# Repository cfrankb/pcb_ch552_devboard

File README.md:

# CH552 DEVBOARD

## Introduction

This is a pcb design for a CH552 DEVBOARD. The board is intended to aid in the development of firmware/prototype for the CH552 and CH554 microcontrollers.

* The Power Switch (Workflow Optimization):
The CH552 enters ISP (programming) mode based on power-on state with a specific pin held. Constantly pulling a USB cable wears out the connector and is inefficient. Your switch demonstrates mechanical sympathy and an understanding of the iterative development cycle.

* The "Ground Forest" (Signal Integrity):
Adding 12x GND pins isn't overkill—it's professional. It allows you to clip a logic analyzer, an oscilloscope probe, and multiple peripherals simultaneously without creating a "rat's nest" of wires sharing a single pin.

* The "Ground Forest" (Signal Integrity): 
 Having 4 LEDs dedicated to the MCU pins allows for immediate visual confirmation of state machines or "heartbeat" signals without needing to wire up external breadboard components.

https://github.com/cfrankb/ch552_drivers/

## Schematic

## Features

 * 4 led to provide indicators
 * 12x GND pins
 * 6x 3.3v pins
 * 6x 5v pins
 * ON/OFF button
 * BOOT and RESET buttons

## Part List

|     | Part #        | REF#                   | Package            |
| --- | ------------- | ---------------------- | ------------------ |
| 1x  | 10u C         | C3                     | 0805               |
| 2x  | 100n C        | C1, C2                 | 1206               |
| 2x  | 10k Resistor  | R1, R4                 | 0805               |
| 6x  | 1k Resistor   | R2, R3, R5, R6, R7, R8 | 0805               |
| 1x  | Green Led     | D1                     | 0805               |
| 5x  | Leds          | D2, D3, D4, D5, D6     | 0805               |
| 1x  | CH552G/CH554G | U1                     | SOP16              |
| 2x  | button        | SW1, SW2               | 6x6x4.3mm DIP      |
| 1x  | USB Connector | J1                     | USB 2.0 Female DIP |
| 1x  | 1x07          | J2                     | 2.54mm pins DIP    |
| 1x  | 2x03          | J3, J5, J6, J7         | 2.54mm pins DIP    |
| 1x  | 1x05          | J4                     | 2.54mm pins DIP    |
| 1x  | 1x04          | J8                     | 2.54mm pins DIP    |
| 1x  | 1x03          | J9                     | SS12D00 DIP *      |

\* You can also use a 2.54mm pin header with a jumper cap.

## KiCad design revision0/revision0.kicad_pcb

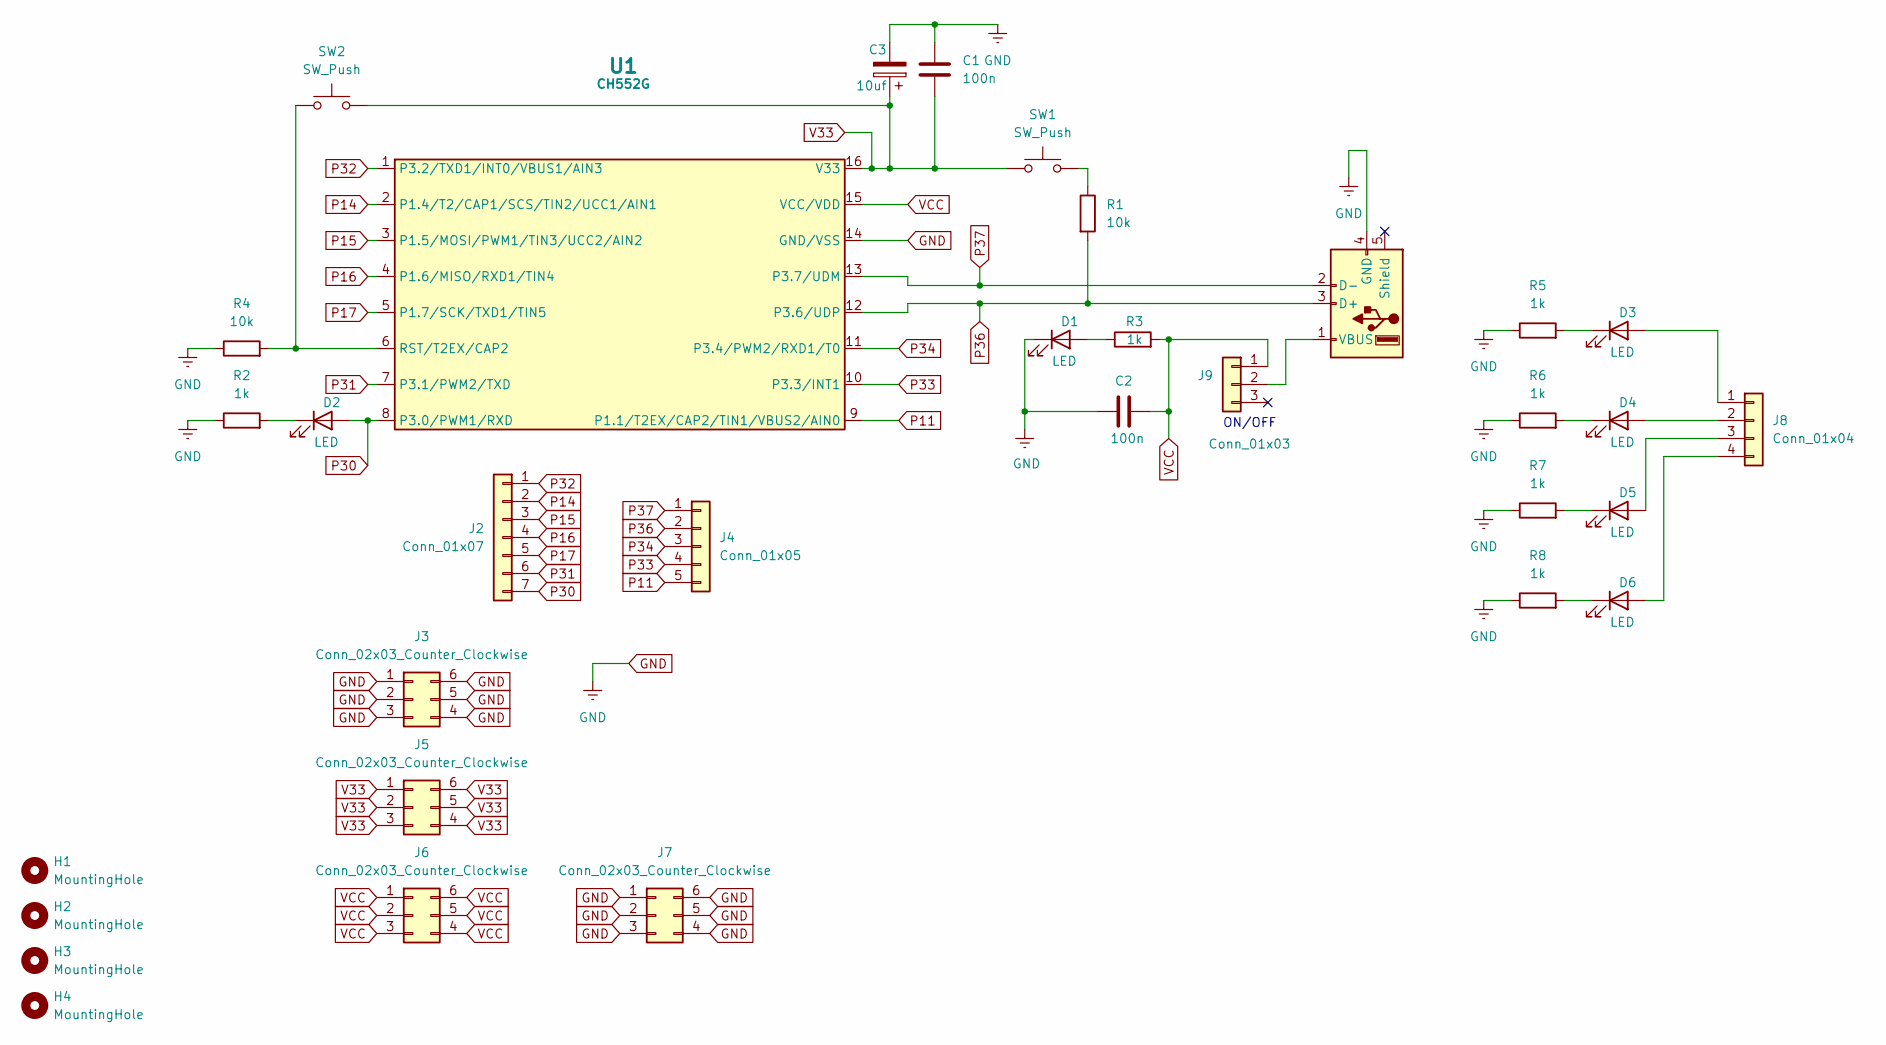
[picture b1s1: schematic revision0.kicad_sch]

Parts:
C1, C2: 100n; C_1206_3216Metric_Pad1.33x1.80mm_HandSolder
C3: 10uf; C_0805_2012Metric_Pad1.18x1.45mm_HandSolder
D1, D2, D3, D4, D5, D6: LED; LED_0805_2012Metric_Pad1.15x1.40mm_HandSolder
H1, H2, H3, H4: MountingHole; MountingHole_3mm
J1: USB1; USB_A_Molex_67643_Horizontal
J2: Conn_01x07; PinHeader_1x07_P2.54mm_Vertical
J3, J5, J6, J7: Conn_02x03_Counter_Clockwise; PinHeader_2x03_P2.54mm_Vertical
J4: Conn_01x05; PinHeader_1x05_P2.54mm_Vertical
J8: Conn_01x04; PinHeader_1x04_P2.54mm_Vertical
J9: Conn_01x03; PinHeader_1x03_P2.54mm_Vertical
R1, R4: 10k; R_0805_2012Metric_Pad1.20x1.40mm_HandSolder
R2, R3, R5, R6, R7, R8: 1k; R_0805_2012Metric_Pad1.20x1.40mm_HandSolder
SW1, SW2: SW_Push; SW_PUSH_6mm_H4.3mm
U1: CH552G; SOP-16_4.55x10.3mm_P1.27mm

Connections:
GND: C1.1, C2.1, C3.2, D1.1 (K), J1.4 (GND), J3.1, J3.2, J3.3, J3.4, J3.5, J3.6, J7.1, J7.2, J7.3, J7.4, J7.5, J7.6, R2.1, R4.1, R5.1, R6.1, R7.1, R8.1, U1.14 (GND/VSS)
unnamed: D1.2 (A), R3.1
unnamed: D2.1 (K), R2.2
unnamed: D3.2 (A), J8.1
unnamed: D3.1 (K), R5.2
unnamed: D4.2 (A), J8.2
unnamed: D4.1 (K), R6.2
unnamed: D5.2 (A), J8.3
unnamed: D5.1 (K), R7.2
unnamed: D6.2 (A), J8.4
unnamed: D6.1 (K), R8.2
unnamed: J1.1 (VBUS), J9.2
unnamed: R1.1, SW1.2
unnamed: R4.2, SW2.1, U1.6 (RST/T2EX/CAP2)
P11: J4.5, U1.9 (P1.1/T2EX/CAP2/TIN1/VBUS2/AIN0)
P14: J2.2, U1.2 (P1.4/T2/CAP1/SCS/TIN2/UCC1/AIN1)
P15: J2.3, U1.3 (P1.5/MOSI/PWM1/TIN3/UCC2/AIN2)
P16: J2.4, U1.4 (P1.6/MISO/RXD1/TIN4)
P17: J2.5, U1.5 (P1.7/SCK/TXD1/TIN5)
P30: D2.2 (A), J2.7, U1.8 (P3.0/PWM1/RXD)
P31: J2.6, U1.7 (P3.1/PWM2/TXD)
P32: J2.1, U1.1 (P3.2/TXD1/INT0/VBUS1/AIN3)
P33: J4.4, U1.10 (P3.3/INT1)
P34: J4.3, U1.11 (P3.4/PWM2/RXD1/T0)
P36: J1.3 (D+), J4.2, R1.2, U1.12 (P3.6/UDP)
P37: J1.2 (D-), J4.1, U1.13 (P3.7/UDM)
V33: C1.2, C3.1, J5.1, J5.2, J5.3, J5.4, J5.5, J5.6, SW1.1, SW2.2, U1.16 (V33)
VCC: C2.2, J6.1, J6.2, J6.3, J6.4, J6.5, J6.6, J9.1, R3.2, U1.15 (VCC/VDD)

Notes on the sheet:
ON/OFF

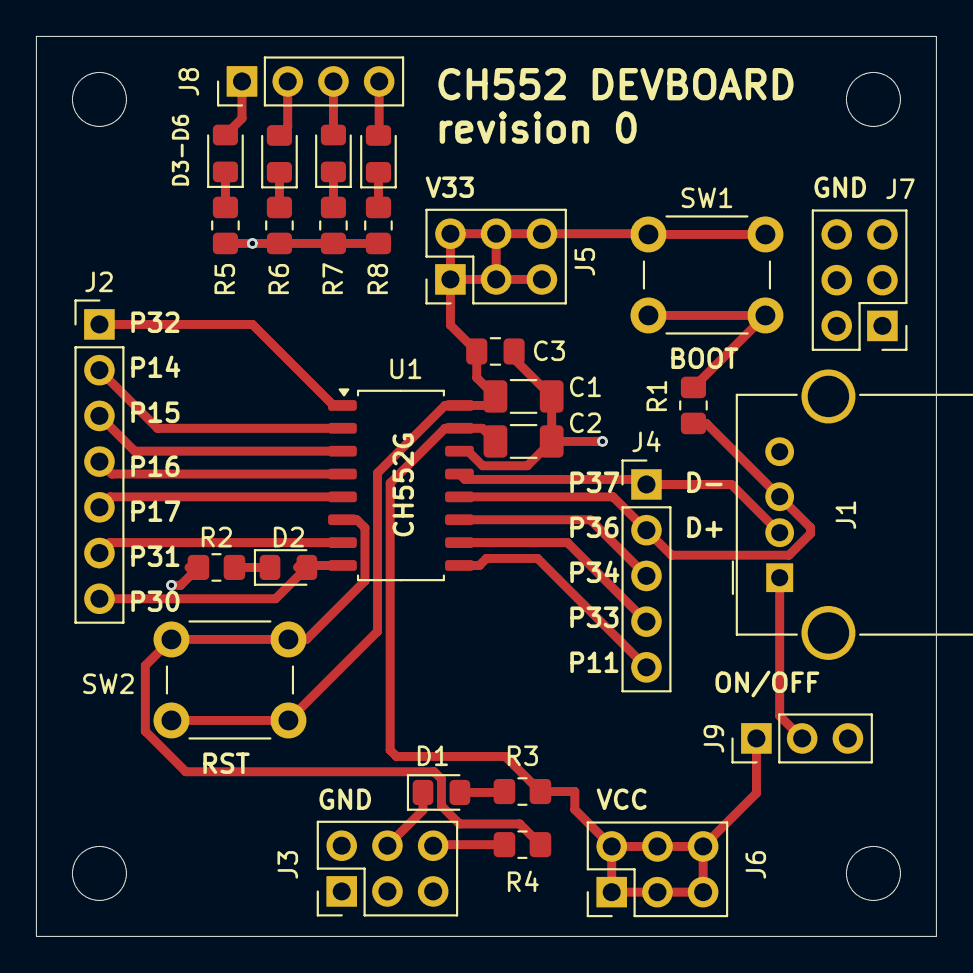
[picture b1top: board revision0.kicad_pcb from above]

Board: 2 copper layers, 50.0 x 50.0 mm, 33 parts (0 on the bottom side), 28 nets.

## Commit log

2024-10-19 added README
2024-10-19 minor fix
2024-10-19 fixed part list
2025-02-26 update project w/ missing footprint
2026-03-05 added schematic
